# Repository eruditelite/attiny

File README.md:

# attiny -- ATTiny84/ATTiny85 Examples using the Raspberry Pi #

## Overview ##

Most of the ATTiny examples seem to be based on the Arduino.  As I
wanted a simple example using the Raspberry Pi (the reason for all of
this is controlling telescopes using lin_guider etc.), I decided to
write this all down so I could remember it later!

## Requirements ##

sudo apt install gcc-avr avr-libc avrdude

Enable SPI and I2C using 'sudo raspi-config'.

Add 'dtoverlay=spi1-3cs' to /boot/config.txt.

systemctl enable pigpiod

## avrdude ##

Speed is one problem... The ATTinys work reliably, at least on a
breadboard, at lower speeds than the default. avrdude's '-b' option
changes the speed of SPI0, but SPI1 runs at 50 KHz no matter what the
value of '-b' is. So, to avoid having to update avrdude, SPI0 must be
used to program both parts. As the parts don't have a chip select,
that must be added externally.

Another problem is pin use, especially on the ATTiny85.

The problem is, that -b doesn't set the speed on SPI1.

./configure --build=arm-linux-gnueabihf --prefix=/usr --includedir=\${prefix}/include --mandir=\${prefix}/share/man --infodir=\${prefix}/share/info --sysconfdir=/etc --localstatedir=/var --disable-silent-rules --libdir=\${prefix}/lib/arm-linux-gnueabihf --libexecdir=\${prefix}/lib/arm-linux-gnueabihf --disable-maintainer-mode --disable-dependency-tracking --enable-versioned-doc=no --enable-doc --enable-linuxgpio

for 84

gpio -g mode 0 in
gpio -g mode 1 in
gpio -g mode 9 alt0
gpio -g mode 10 alt0
gpio -g mode 11 alt0
gpio -g mode 22 out
gpio -g write 22 0

sudo avrdude -p t85 -P /dev/spidev0.0 -c linuxspi -b 5000 -U flash:w:flash.hex

gpio -g mode 22 out
gpio -g write 22 1
gpio -g mode 22 in
gpio -g mode 0 alt0
gpio -g mode 1 alt0
gpio -g mode 9 in
gpio -g mode 10 in
gpio -g mode 11 in

## Basic Functionality ##

At the top, is a template that works on either the ATTiny84 or
ATTiny85.  It includes a way to use i2c, and a system tick, but not
much else.  For inputs, outputs, interrupts, etc. see the examples.

For the test setup, a Raspberry Pi is used to program the ATTinys and
read/write "registers.  Since the test board will have two parts (one
ATTiny84 and one ATTiny85), separate SPI and I2C interfaces are used
for each.  The EEPROM I2C interface (pins 0 and 1) and SPI0 (pins 9,
10, and 11) are used for the ATTiny84.  For the ATTiny85, I2C (pins 3
and 3) and SPI1 (pins 19, 20, and 21) are used.  Note that the EEPROM
clock and data pins do not include a pull up resitor!  A 1K resitor is
include from each to +3.3V.

BCM 22 is used as a reset, connected to both ATTinys.

In some cases, multiple pins from the Raspberry Pi connect to a single
pin on the ATTiny.  All pins related to the function not being used
(I2C or SPI) should be tristated.  In this document, the BCM numers
will be used and the 'gpio' command will be used with the '-g' option.
Details are available in makefile.attiny84 and makefile.attiny85.
Both of those makefiles include macros to switch the Raspberry
Pi/ATTiny connection to SPI mode or to I2C mode.

In addition to the obvious connections -- 3.3 V and Common -- connect
as follows.

## I2C ##

## Tick ##

Using the "blink" example (see below), the tick can be measured -- just set the rate of the LED to 16 ms.  Measuring the part I used to test attiny resulted in a bit more, 17.8 ms.

## Examples ##

In the following examples, the I2C address is 7 for no particular
reason.  The only other consistent difference is the macro for the
"Timer Interrupt Mask Register".  The ATTiny84 has TIMSK0 and the
ATTiny85 has TIMSK.

### ATTiny Simple ###

No external connections, just I2C.  Three "registers" are created, 1,
2, and 4 bytes.  All registers can be read or written using 'access'.
To run, do the following.

1. 'cd example84/simple' OR 'cd example85/simple'.
2. 'make reset ; make flash'.
3. 'make access'.

After the above, access should display the values of the registers,
and allow them to be changed.

```text
[ pi@raspberrypi ] ./access
Project: 0x0002 Version: 0x0001
dummys are 0x11 0x2222 0x44444444
[ pi@raspberrypi ] ./access -1 0x12 -2 0x3456 -4 0x789abcde
Project: 0x0002 Version: 0x0001
dummys are 0x12 0x3456 0x789abcde
[ pi@raspberrypi ] ./access
Project: 0x0002 Version: 0x0001
dummys are 0x12 0x3456 0x789abcde
[ pi@raspberrypi ] ./access -v
--> Starting pigpio with (localhost, 8888)
--> Opening pigpio I2C with (, 2, 3, 20000)
zip: 04 07 02 07 01 00 03 02 06 02 03 00 
buf: cd ba 
zip: 04 07 02 07 01 01 03 02 06 02 03 00 
buf: 02 00 
zip: 04 07 02 07 01 02 03 02 06 02 03 00 
buf: 01 00 
Project: 0x0002 Version: 0x0001
zip: 04 07 02 07 01 03 03 02 06 01 03 00 
buf: 12 
zip: 04 07 02 07 01 04 03 02 06 02 03 00 
buf: 56 34 
zip: 04 07 02 07 01 05 03 02 06 04 03 00 
buf: de bc 9a 78 
dummys are 0x12 0x3456 0x789abcde
```

To test accesses multiple times add '-t <number>'. Each test will,
with no other options, simply read the available registers. To write
as well as read, add some combination of the -1, -2, and -4 options.

### ATTiny Blink ###

Blink a few LEDs using the "tick" (based on the watchdog timer, see
tick.h/tick.c).  On the ATTiny 84, the outputs are PB0, PB1, and PB2;
on the ATTiny84, the outputs are PB1, PB3, and PB4.

'access' provides a way to change the blink rate of each LED.  Since
this example uses a tick based on the watchdog timer, the rate must be
a multiple of 16 ms.

Connect the output pins to the following circuit.

### ATTiny Square ###

Square wave output on PB1.  OCR1A is the "percentage on" (0...255);
the initial value is 127.  Use a low pass filter to smooth the output.
Resistor and capacitor values will depend on the load etc.

And the result is...

### ATTiny Wave (Not Implemented on ATTiny84) ###

This example uses timer/counter 1 for PWM output on PB4 and
timer/counter 0 as a trigger to change the sample.  The samples are
stored in eeprom.  An example of generating sample sets is provited by
wavegen.c (after compiling, see ./wavegen -h for a description).
Writing the sample to eeprom is handled by the 'eeprom' target in
makefile.attiny.  First a binary is created by wavegen, then the make
target converts the binary to Intel hex and writes it to the eeprom
using avrdude.

As the interrupts from timer/counter 0 are fairly fast, I2C is not
supported.

Use a low pass filter on the output as follows.

### ATTiny ADC (Not Implemented on ATTiny84) ###

### ATTiny Activity (Not Implemented on ATTiny84) ###

## About Pin Ordering ##

It seems obvious that pin 1 on the chip should go to pin one on the header... at least until you start routing the board!

2
3
5
6
13
12
11
10
8

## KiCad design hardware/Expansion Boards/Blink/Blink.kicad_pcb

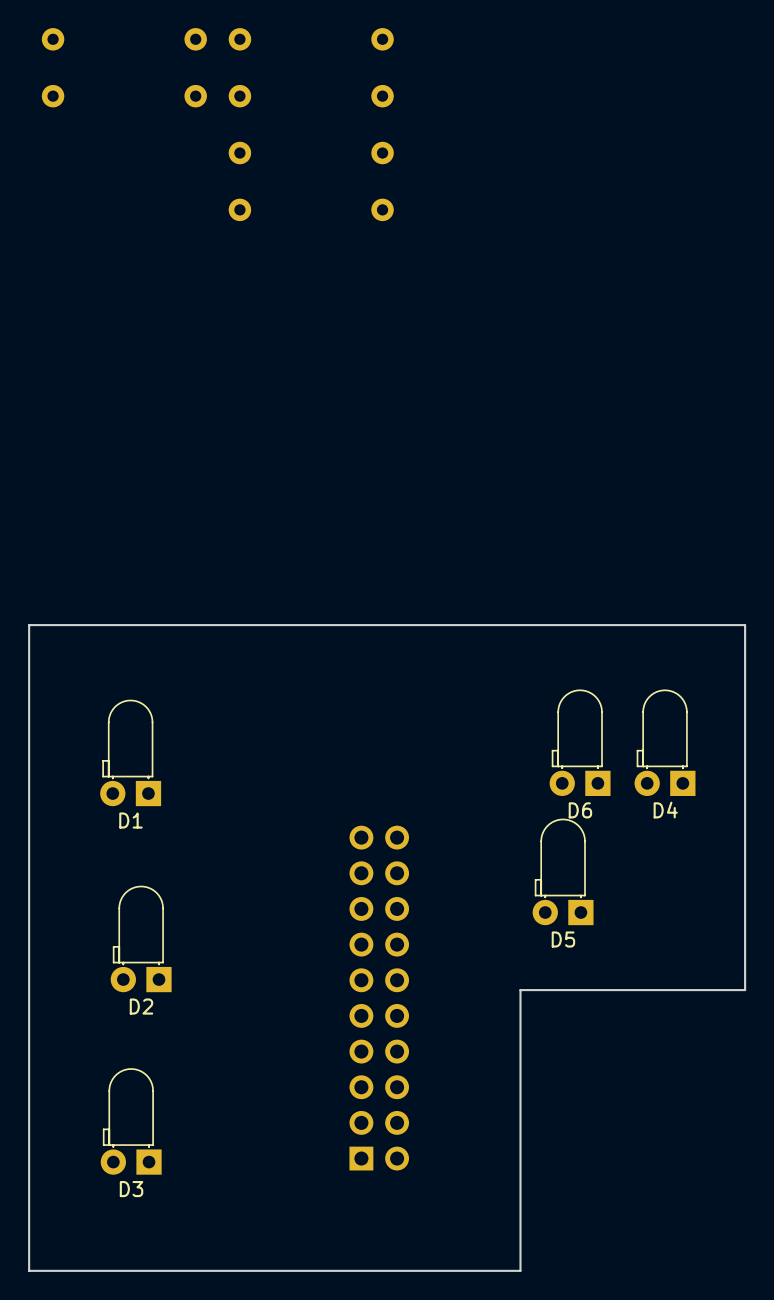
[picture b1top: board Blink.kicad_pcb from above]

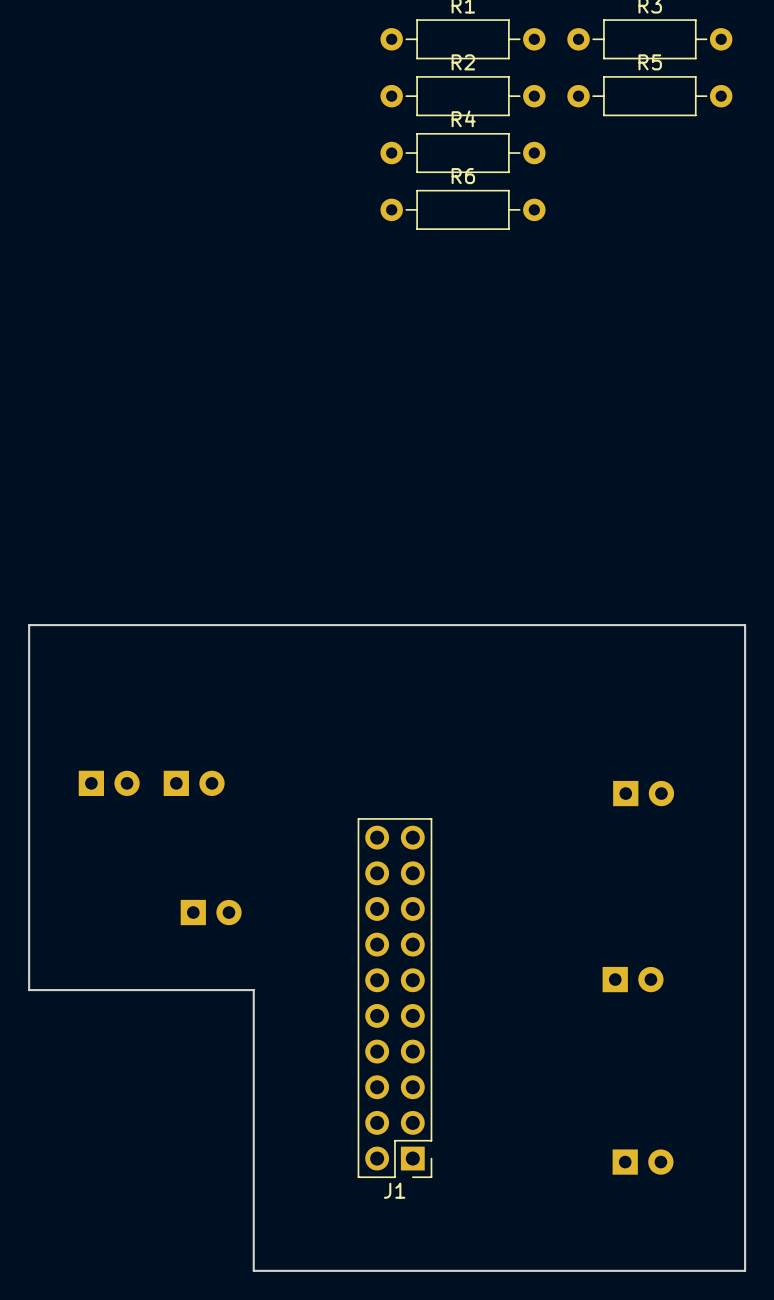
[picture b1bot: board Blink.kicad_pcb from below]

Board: 2 copper layers, 51.0 x 46.0 mm, 13 parts (7 on the bottom side), 13 nets, no tracks yet.

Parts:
D1, D2, D3, D4, D5, D6: LED; LED_D3.0mm_Horizontal_O1.27mm_Z2.0mm
J1: Daughter Board Connector; PinHeader_2x10_P2.54mm_Vertical
R1, R2, R3, R4, R5, R6: 330; R_Axial_DIN0207_L6.3mm_D2.5mm_P10.16mm_Horizontal

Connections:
/ATtiny84_PB0: D1.2, J1.8
/ATtiny84_PB1: D2.2, J1.6
/ATtiny84_PB2: D3.2, J1.5
/ATtiny85_PB1: D4.2, J1.12
/ATtiny85_PB3: D5.2, J1.18
/ATtiny85_PB4: D6.2, J1.16
GND: J1.2, J1.4, R1.2, R2.2, R3.2, R4.2, R5.2, R6.2
unnamed: D1.1, R1.1
unnamed: D2.1, R2.1
unnamed: D3.1, R3.1
unnamed: D4.1, R4.1
unnamed: D5.1, R5.1
unnamed: D6.1, R6.1

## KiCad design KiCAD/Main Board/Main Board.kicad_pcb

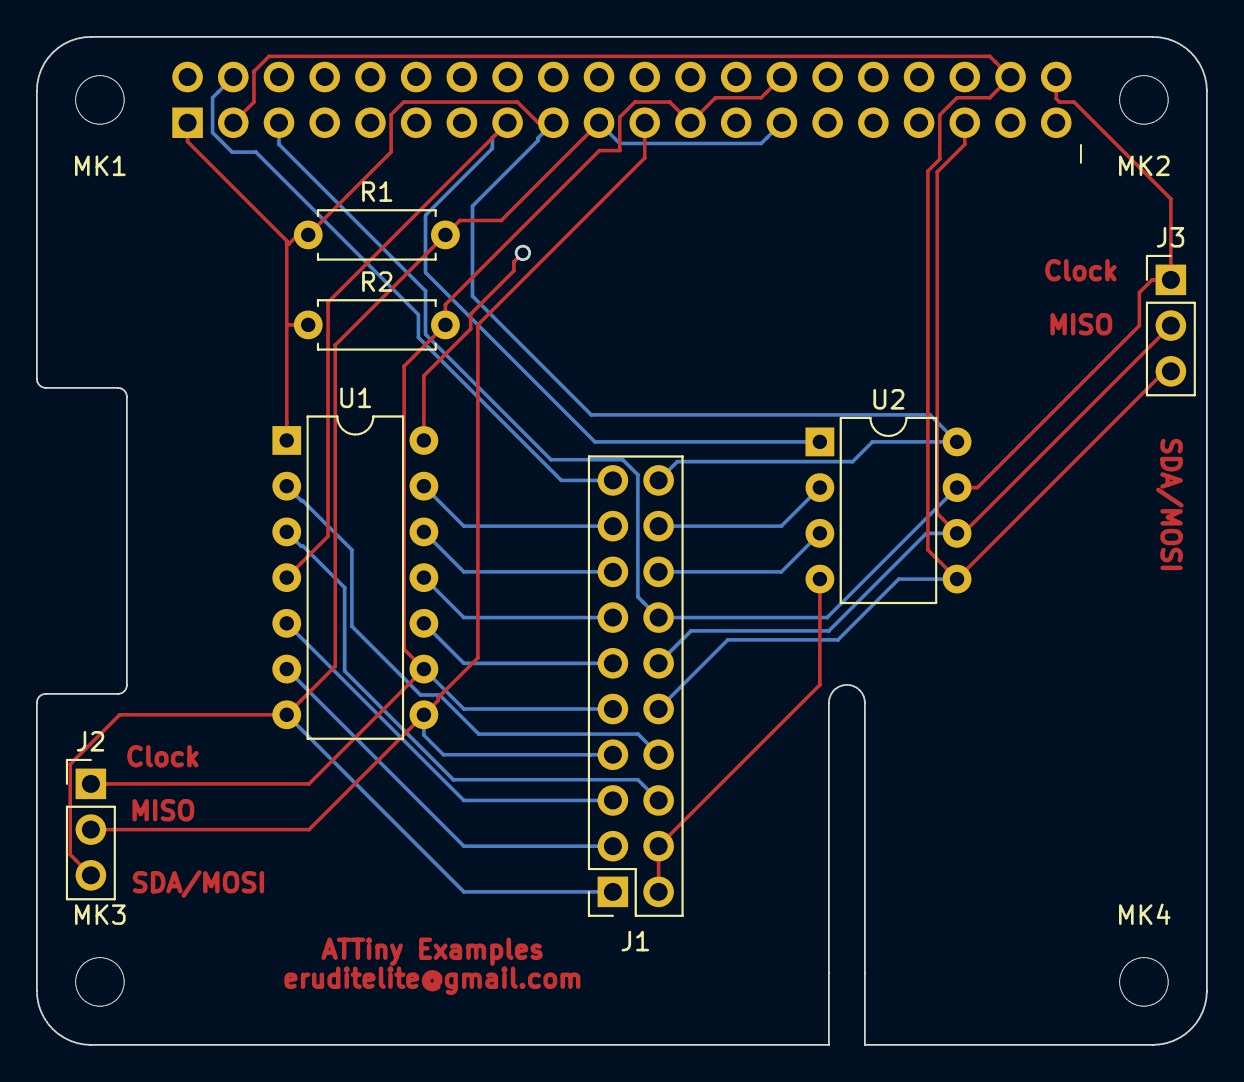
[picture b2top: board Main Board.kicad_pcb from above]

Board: 2 copper layers, 65.0 x 56.0 mm, 12 parts (1 on the bottom side), 20 nets.

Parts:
J1: Daughter Board Connector; PinSocket_2x10_P2.54mm_Vertical
J2: ATtiny84 I2C/SPI Debug; PinHeader_1x03_P2.54mm_Vertical
J3: ATtiny85 I2c/SPI Debug; PinHeader_1x03_P2.54mm_Vertical
MK1, MK2, MK3, MK4: M2.5; MountingHole_2.7mm_M2.5
P1: Raspberry Pi; PinSocket_2x20_P2.54mm_Vertical
R1, R2: 1K; R_Axial_DIN0207_L6.3mm_D2.5mm_P7.62mm_Horizontal
U1: ATtiny84-20PU; DIP-14_W7.62mm
U2: ATtiny85-20PU; DIP-8_W7.62mm

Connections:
+3V3: J1.20, P1.1, P1.17, R1.1, R2.1, U1.1, U2.8
+5V: J1.19, P1.4
/GPIO2(SDA1): J1.10, J3.3, P1.3, P1.38, U2.5
/GPIO9(SPI0_MISO): J1.7, J2.2, P1.21, U1.8
/GPIO10(SPI0_MOSI): J1.1, J2.3, P1.19, P1.27, R1.2, U1.7
/GPIO11(SPI0_SCK): J1.9, J2.1, P1.23, P1.28, R2.2, U1.9
/GPIO19(SPI1_MISO): J1.12, J3.2, P1.35, U2.6
/GPIO21(SPI1_SCK): J1.14, J3.1, P1.5, P1.40, U2.7
/GPIO22(GEN3): P1.15, U1.4, U2.1
GND: J1.2, J1.4, P1.39, U1.14, U2.4
unnamed: J1.3, U1.6
unnamed: J1.5, U1.5
unnamed: J1.6, U1.3
unnamed: J1.8, U1.2
unnamed: J1.11, U1.10
unnamed: J1.13, U1.11
unnamed: J1.15, U1.12
unnamed: J1.16, U2.3
unnamed: J1.17, U1.13
unnamed: J1.18, U2.2

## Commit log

2018-05-15 Turn Off the LEDs
    LEDs were used in the orignal debug...
2018-05-15 Verify the Magic Number
2018-05-16 Reorganization
    Move the callbacks to a different source file and
    add a header.
2018-05-17 Add a Timer
2018-05-17 Add a "work" Function and Other Cleanup
    Instead of doing everything in main(), just initialize
    and then call work().
    Use the new usitwislave code that returns after initialization
    and provides a function to respond to i2c request.
    Add a delay function that checks for i2c requests fairly
    often.
2018-05-17 Create Examples
    At the top level, work() does nothing but check
    for I2C messages. The examples show how to use
    the pins. Initial example blinks one of the LEDs.
2018-05-18 Lots of Cleanup
    This is, probably, the first usable version.
2018-05-18 Full Basic Support
    This is one way to create a PWM, as the duty
    cycle can be controlled. No interrupt handler
    is required. Only square wave output.
2018-05-18 Combine some Files
    As the time, i2c callback, and work functions
    share global variables, put them in them same
    file.
2018-05-18 Rename 'examples' and Update Layout
    Update to the latest source code layout and
    change the name of examples to examples85 since
    the target is attiny85.
2018-05-18 Add Support for ATTiny84
2018-05-18 Add a "blink" Example for ATTiny84
2018-05-18 Enhance the ATTiny85 "blink" Example
    Allow the delay to be set via access instead of
    just displaying and dividing by 2.
2018-05-20 Major Cleanup... Use Macros
2018-05-20 Make the I2C Address an Input Parameter
2018-05-20 Clean Up
    As both ATTiny84 and ATTiny85 are now supported, change
    the name to attiny.h.
    Set the I2C address to 4 for ATTiny84 and 5 for ATTiny85.
2018-05-20 Example of Using pigpio for I2C Access
2018-05-21 Update the I2C Access
    Use the 'pigpiod' bit banged methods to work around
    the Raspberry Pi's bad I2C hardware.
2018-05-21 Update Option Handling
    Also adds a "test" option.
2018-05-21 Clean up the Makefile and access.c
2018-05-21 Set the I2C Data and Clock Pins based on Target
2018-05-22 Update to the new Build System
2018-05-23 Use the new Build System
2018-05-23 Clean Up
2018-05-23 Use Timer/Counter0 as a Tick to Check I2C
2018-05-23 Change the Default Speed to 10000
2018-05-23 What? Documentation??
2018-05-25 Something Different
2018-05-25 Simplified Layout, and Optional Features
    Make ticks and i2c optional...
2018-05-27 Reorganize
2018-05-27 Simplify Setup of the PWM
2018-05-28 Add a "square" Example on ATTiny84
2018-05-28 Add the example84/square Example
2018-05-28 Make I2C Handling More Flexible
    Previously, libi2c configure timer0 to generate
    interrupts used to check for and handle i2c
    messages. Instead, leave it up to the application
    (main.c) to check for messages is some appropriate
    way.
2018-05-29 Add Wave Examples
2018-06-08 Add 'wavegen' to Generate Wavform Data Tables
2018-06-08 A Cleaned Up Wave Example for ATTiny85
2018-06-11 Major Cleanup of the Makefiles
2018-06-15 Fix a Bug in 16 bit Accesses
2018-06-15 Change the Mode to Executable
2018-06-15 Add a "fuse_1M" Target for Low Power Examples
    By default, all the examples run at 8 MHz. If power
    is a concern, running a 1 MHz helps quite a bit! Add
    fuse_1M to burn the fuses to run at 1 MHz.
2018-06-15 Update the Directories in scripts/build.sh
    Don't try to build the top directory, it is now just
    a template!
    Add examples85/adc and example85/activity.
2018-06-15 Add 'adc' and 'activity' Examples for ATTiny85
2018-06-16 Add "Simple" Examples for ATTiny84 and ATTiny85
2018-06-17 Add a Third LED
2018-06-18 Include 'sawtooth' in the Help Output
2018-06-18 Update the "square" and "wave" Examples in 85
2018-06-18 Update to the Format
2018-06-18 Use 7 as the I2C Address
2018-06-18 More Scope Images
2019-03-19 Add KiCAD Projects
    Add a project for the main board, and an expansion board
    template.
2019-03-19 OSHPARK Order Number chh9sp7Z
2019-03-20 Ordered Three Blink Boards
    OSHPARK order number is XsFSM6ru.
2019-03-22 Update the Requirements
2019-03-22 Remane the KiCAD Directory to the More General 'hardware'
2019-03-22 Busy Wait for I2C Messages
2019-03-22 Add and ADC Sample for the ATTiny84
2019-03-22 Clean Up the 'simple' Examples
    There were errors in the access 'help' output, and more explanation of
    using 'access' was needed in README.md.
2019-04-02 Add a Work-Around for release_1.0
    Switch LEDs 0 and 1 in example85.
2019-04-02 Revert "Add a Work-Around for release_1.0"
    This reverts commit 4719e37ea200724a4972281ce557b1bdc3f5225f.
2019-04-02 New Blink Expansion Board
2019-04-05 Add Power Control and Use SPI0 Only
    As SPI1 exists, it seems an easy way to program two chips that
    don't have chip select or enable pins. BUT, avrdude, which I'm
    using to program the AVRs, only handles the baud rate correctly
    on SPI0. That being the case, enhance the circuit so that two
    GPIO pins are used to power on or off the AVRs.
2019-04-09 Add a Delay in the Reset Sequence
2019-04-11 Use a Common I2C Bus
    Instead of using separate I2C busses, use the one on
    pins 2 and 3 for both devices. By default, make the
    I2C address for the ATTiny84 be 4 and for the ATTiny85,
    5.
2019-04-11 Add a LA Configuration
    Logic analyzer setup for I2C and SPI.
2019-04-15 The New (v2) Board
2019-04-25 Update Description of SPI Issues
2019-04-30 Fix an Error in the v2 Board
    The custom footprint for the quad buffer had two pin 12s!
    Updated the silk to release_2_1 as well.
